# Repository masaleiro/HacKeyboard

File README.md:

# HacKeyboard

Open hardware mechanical keyboard, by Mário Saleiro

HacKeyboard is a mechanical keyboard built from scratch using SMK Alps Mount switches from an old Monterey K108 keyboard and Alps compatible keycaps from an old NGS keyboard.

It has several features that are not usually found in commercial keyboards:
- Internal keylogger;
- Macro recording capabilites;
- Internal USB Hub 2.0;
- Internal (hidden) 8GB flash drive;
- Micro USB Port for connecting peripherals;
- Customizable LED colors;
- Customizable LED effects;

The whole build process is documented and available here: http://www.instructables.com/id/HacKeyboard-a-mechanical-keyboard-built-from-scrat/

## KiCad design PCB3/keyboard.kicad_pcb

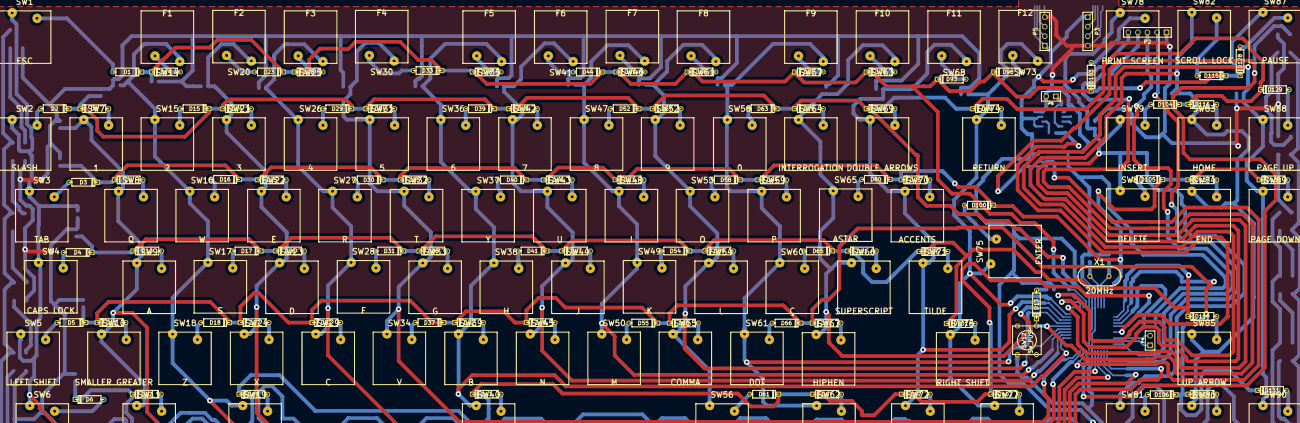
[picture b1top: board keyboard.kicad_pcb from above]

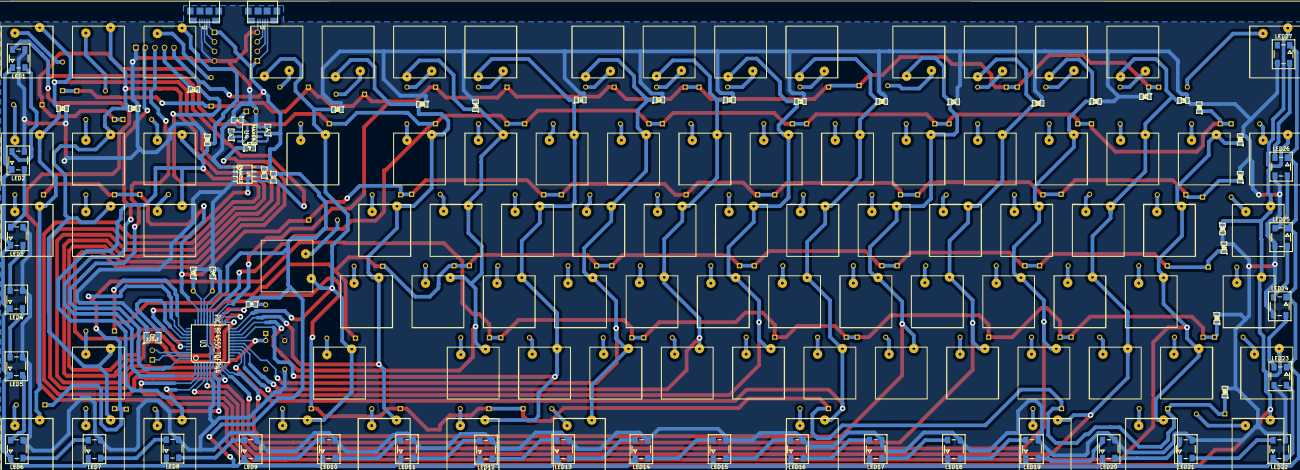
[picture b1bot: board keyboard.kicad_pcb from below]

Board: 2 copper layers, 250 parts (66 on the bottom side), 160 nets.

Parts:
C1: 100nF; SM0805
C2: 220uF; SM1210
C3, C4, C5: C; SM0805
C6, C7: 22pF; SM0805
D1, D2, D3, D4, D5, D6, D8, D9, D10, D11, D12, D14, D15, D16, D17, D18, D19, D23, D24, D25, D26, D27, D28, D29, D30, D31, D32, D33, D34, D35, D36, D37, D38, D39, D40, D41, D42, D43, D44, D45, D46, D47, D48, D51, D52, D53, D54, D55, D56, D57, D58, D59, D60, D61, D62, D63, D64, D65, D66, D67, D78, D79, D80, D81, D82, D93, D94, D95, D96, D97, D98, D99, D100, D101, D102, D103, D104, D105, D106, D115, D116, D117, D118, D119, D128, D129, D130, D131: DIODE; D3
D13: 1N4148; D3
LED1, LED2, LED3, LED4, LED5, LED6, LED7, LED8, LED9, LED10, LED11, LED12, LED13, LED14, LED15, LED16, LED17, LED18, LED19, LED20, LED21, LED22, LED23, LED24, LED25, LED26, LED27: WS2812B; PLCC4-5050
P2: PROG_CONN; PIN_ARRAY_5x1
P3, P5: CONN_4; PIN_ARRAY_4x1
P4, P6: CONN_2; PIN_ARRAY_2X1
R1: R; SM0805
R2, R6, R7: 1K; SM0805
R51, R52, R53, R54, R55, R56, R57, R58, R59, R60, R61, R62, R63, R64, R65, R66, R67, R68, R69, R70, R71, R72, R73: 10K; SM0805
SW1: ESC; ALPS-SWITCH
SW2: SLASH; ALPS-SWITCH
SW3: TAB; ALPS-SWITCH
SW4: CAPS LOCK; ALPS-SWITCH
SW5: LEFT SHIFT; ALPS-SWITCH
SW6: LEFT CONTROL; ALPS-SWITCH
SW7: 1; ALPS-SWITCH
SW8: Q; ALPS-SWITCH
SW9: A; ALPS-SWITCH
SW10: SMALLER GREATER; ALPS-SWITCH
SW11: LEFT SUPER; ALPS-SWITCH
SW12: SW_PUSH; SW_PUSH_SMALL
SW14: F1; ALPS-SWITCH
SW15: 2; ALPS-SWITCH
SW16: W; ALPS-SWITCH
SW17: S; ALPS-SWITCH
SW18: Z; ALPS-SWITCH
SW19: LEFT ALT; ALPS-SWITCH
SW20: F2; ALPS-SWITCH
SW21: 3; ALPS-SWITCH
SW22: E; ALPS-SWITCH
SW23: D; ALPS-SWITCH
SW24: X; ALPS-SWITCH
SW25: F3; ALPS-SWITCH
SW26: 4; ALPS-SWITCH
SW27: R; ALPS-SWITCH
SW28: F; ALPS-SWITCH
SW29: C; ALPS-SWITCH
SW30: F4; ALPS-SWITCH
SW31: 5; ALPS-SWITCH
SW32: T; ALPS-SWITCH
SW33: G; ALPS-SWITCH
SW34: V; ALPS-SWITCH
SW35: F5; ALPS-SWITCH
SW36: 6; ALPS-SWITCH
SW37: Y; ALPS-SWITCH
SW38: H; ALPS-SWITCH
SW39: B; ALPS-SWITCH
SW40: SPACEBAR; ALPS-SWITCH
SW41: F6; ALPS-SWITCH
SW42: 7; ALPS-SWITCH
SW43: U; ALPS-SWITCH
SW44: J; ALPS-SWITCH
SW45: N; ALPS-SWITCH
SW46: F7; ALPS-SWITCH
SW47: 8; ALPS-SWITCH
SW48: I; ALPS-SWITCH
SW49: K; ALPS-SWITCH
SW50: M; ALPS-SWITCH
SW51: F8; ALPS-SWITCH
SW52: 9; ALPS-SWITCH
SW53: O; ALPS-SWITCH
SW54: L; ALPS-SWITCH
SW55: COMMA; ALPS-SWITCH
SW56: RIGHT ALT; ALPS-SWITCH
SW57: F9; ALPS-SWITCH
SW58: 0; ALPS-SWITCH
SW59: P; ALPS-SWITCH
SW60: Ç; ALPS-SWITCH
SW61: DOT; ALPS-SWITCH
SW62: RIGHT SUPER; ALPS-SWITCH
SW63: F10; ALPS-SWITCH
SW64: INTERROGATION; ALPS-SWITCH
SW65: ASTAR; ALPS-SWITCH
SW66: SUPERSCRIPT; ALPS-SWITCH
SW67: HIPHEN; ALPS-SWITCH
SW68: F11; ALPS-SWITCH
SW69: DOUBLE ARROWS; ALPS-SWITCH
SW70: ACCENTS; ALPS-SWITCH
SW71: TILDE; ALPS-SWITCH
SW72: MENU; ALPS-SWITCH
SW73: F12; ALPS-SWITCH
SW74: RETURN; ALPS-SWITCH
SW75: ENTER; ALPS-SWITCH
SW76: RIGHT SHIFT; ALPS-SWITCH
SW77: RIGHT CONTROL; ALPS-SWITCH
SW78: PRINT SCREEN; ALPS-SWITCH
SW79: INSERT; ALPS-SWITCH
SW80: DELETE; ALPS-SWITCH
SW81: LEFT ARROW; ALPS-SWITCH
SW82: SCROLL LOCK; ALPS-SWITCH
SW83: HOME; ALPS-SWITCH
SW84: END; ALPS-SWITCH
SW85: UP ARROW; ALPS-SWITCH
SW86: DOWN ARROW; ALPS-SWITCH
SW87: PAUSE; ALPS-SWITCH
SW88: PAGE UP; ALPS-SWITCH
SW89: PAGE DOWN; ALPS-SWITCH
SW90: RIGHT ARROW; ALPS-SWITCH
U1: MICRO-B_USB_CHG; MICRO-B_USB
U2: MICRO-B_USB_HUB; MICRO-B_USB
U3: PIC18F4550_TQFP44; TQFP44
U4: MAX682; SO8E
U5: 24AA512; so-8
X1: 20MHz; HC-49V

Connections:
/C1: R57.1, SW1.1, SW2.1, SW3.1, SW4.1, SW5.1, SW6.1, U3.2
/C2: R59.1, SW7.1, SW8.1, SW9.1, SW10.1, SW11.1, U3.3
/C3: R61.1, SW14.1, SW15.1, SW16.1, SW17.1, SW18.1, SW19.1, U3.4
/C4: R63.1, SW20.1, SW21.1, SW22.1, SW23.1, SW24.1, U3.5
/C5: R65.1, SW25.1, SW26.1, SW27.1, SW28.1, SW29.1, U3.10
/C6: R67.1, SW30.1, SW31.1, SW32.1, SW33.1, SW34.1, U3.11
/C7: R68.1, SW35.1, SW36.1, SW37.1, SW38.1, SW39.1, SW40.1, U3.14
/C8: R69.1, SW41.1, SW42.1, SW43.1, SW44.1, SW45.1, U3.15
/C9: R70.1, SW46.1, SW47.1, SW48.1, SW49.1, SW50.1, U3.16
/C10: R71.1, SW51.1, SW52.1, SW53.1, SW54.1, SW55.1, SW56.1, U3.17
/C11: R72.1, SW57.1, SW58.1, SW59.1, SW60.1, SW61.1, SW62.1, U3.19
/C12: R73.1, SW63.1, SW64.1, SW65.1, SW66.1, SW67.1, U3.20
/C13: R58.2, SW68.1, SW69.1, SW70.1, SW71.1, SW72.1, U3.21
/C14: R60.2, SW73.1, SW74.1, SW75.1, SW76.1, SW77.1, U3.22
/C15: R62.2, SW78.1, SW79.1, SW80.1, SW81.1, U3.23
/C16: R64.2, SW82.1, SW83.1, SW84.1, SW85.1, SW86.1, U3.24
/C17: R66.2, SW87.1, SW88.1, SW89.1, SW90.1, U3.25
/GND: C2.1, C3.2, C5.2, C6.2, C7.2, LED1.3, LED2.3, LED3.3, LED4.3, LED5.3, LED6.3, LED7.3, LED8.3, LED9.3, LED10.3, LED11.3, LED12.3, LED13.3, LED14.3, LED15.3, LED16.3, LED17.3, LED18.3, LED19.3, LED20.3, LED21.3, LED22.3, LED23.3, LED24.3, LED25.3, LED26.3, LED27.3, P2.1, P3.4, P5.4, P6.2, R51.2, R52.2, R53.2, R54.2, R55.2, R56.2, R57.2, R58.1, R59.2, R60.1, R61.2, R62.1, R63.2, R64.1, R65.2, R66.1, R67.2, R68.2, R69.2, R70.2, R71.2, R72.2, R73.2, SW12.1, U1.5, U2.5, U3.6, U3.29, U4.4, U4.5, U5.1, U5.2, U5.3, U5.4, U5.7
/R1: D1.2, D14.2, D23.2, D28.2, D33.2, D38.2, D44.2, D51.2, D56.2, D62.2, D78.2, D93.2, D98.2, D103.2, D115.2, D128.2, R51.1, U3.26
/R2: D2.2, D8.2, D15.2, D24.2, D29.2, D34.2, D39.2, D45.2, D52.2, D57.2, D63.2, D79.2, D94.2, D99.2, D104.2, D116.2, D129.2, R52.1, U3.27
/R3: D3.2, D9.2, D16.2, D25.2, D30.2, D35.2, D40.2, D46.2, D53.2, D58.2, D64.2, D80.2, D95.2, D100.2, D105.2, D117.2, D130.2, R53.1, U3.32
/R4: D4.2, D10.2, D17.2, D26.2, D31.2, D36.2, D41.2, D47.2, D54.2, D59.2, D65.2, D81.2, D96.2, D101.2, D118.2, R54.1, U3.35
/R5: D5.2, D11.2, D18.2, D27.2, D32.2, D37.2, D42.2, D48.2, D55.2, D60.2, D66.2, D82.2, D106.2, D119.2, D131.2, R55.1, U3.36
/R6: D6.2, D12.2, D19.2, D43.2, D61.2, D67.2, D97.2, D102.2, R56.1, U3.38
/RST: C1.2, D13.2, SW12.2, U3.18
/Rx: P2.2, U3.1
/SCK: R6.1, U3.9, U5.6
/SDA: LED1.4, R7.2, U3.8, U5.5
/SW_PEN: R1.1, U3.40
/Tx: P2.3, U3.44
/VCC: C3.1, LED1.1, LED2.1, LED3.1, LED4.1, LED5.1, LED6.1, LED7.1, LED8.1, LED9.1, LED10.1, LED11.1, LED12.1, LED13.1, LED14.1, LED15.1, LED16.1, LED17.1, LED18.1, LED19.1, LED20.1, LED21.1, LED22.1, LED23.1, LED24.1, LED25.1, LED26.1, LED27.1, P2.5, P3.1, P5.1, R2.2, R6.2, R7.1, U1.1, U2.1, U3.7, U3.28, U4.1, U4.3, U5.8
/VCC2: C5.1, P6.1, U4.8
unnamed: C1.1, P2.4
unnamed: C2.2, U3.37
unnamed: D115.1, SW82.2
unnamed: D130.1, SW89.2
unnamed: D129.1, SW88.2
unnamed: D128.1, SW87.2
unnamed: D131.1, SW90.2
unnamed: D116.1, SW83.2
unnamed: D117.1, SW84.2
unnamed: D118.1, SW85.2
unnamed: D119.1, SW86.2
unnamed: D13.1, R2.1
unnamed: P4.2, U3.42
unnamed: P4.1, U3.43
unnamed: P5.3, U1.3
unnamed: P5.2, U1.2
unnamed: P3.3, U2.3
unnamed: P3.2, U2.2
unnamed: D61.1, SW56.2
unnamed: D60.1, SW55.2
unnamed: D67.1, SW62.2
unnamed: D66.1, SW61.2
unnamed: D65.1, SW60.2
unnamed: D64.1, SW59.2
unnamed: D63.1, SW58.2
unnamed: D62.1, SW57.2
unnamed: D46.1, SW43.2
unnamed: D44.1, SW41.2
unnamed: D45.1, SW42.2
unnamed: D47.1, SW44.2
unnamed: D48.1, SW45.2
unnamed: D53.1, SW48.2
unnamed: D59.1, SW54.2
unnamed: D58.1, SW53.2
unnamed: D57.1, SW52.2
unnamed: D56.1, SW51.2
unnamed: D55.1, SW50.2
unnamed: D54.1, SW49.2
unnamed: D52.1, SW47.2
unnamed: D51.1, SW46.2
unnamed: D102.1, SW77.2
unnamed: D101.1, SW76.2
unnamed: D100.1, SW75.2
unnamed: D99.1, SW74.2
unnamed: D98.1, SW73.2
unnamed: D103.1, SW78.2
unnamed: D106.1, SW81.2
unnamed: D105.1, SW80.2
unnamed: D104.1, SW79.2
unnamed: D82.1, SW67.2
unnamed: D81.1, SW66.2
unnamed: D80.1, SW65.2
unnamed: D79.1, SW64.2
unnamed: D78.1, SW63.2
unnamed: D97.1, SW72.2
unnamed: D93.1, SW68.2
unnamed: D94.1, SW69.2
unnamed: D95.1, SW70.2
unnamed: D96.1, SW71.2
unnamed: LED21.2, LED22.4
unnamed: LED22.2, LED23.4
unnamed: LED16.2, LED17.4
unnamed: LED24.2, LED25.4
unnamed: LED23.2, LED24.4
unnamed: LED20.2, LED21.4
unnamed: LED19.2, LED20.4
unnamed: LED17.2, LED18.4
unnamed: LED18.2, LED19.4
unnamed: C4.1, U4.7
unnamed: C4.2, U4.6
unnamed: R1.2, U4.2
unnamed: LED25.2, LED26.4
unnamed: LED26.2, LED27.4
unnamed: LED4.2, LED5.4
unnamed: LED6.2, LED7.4
unnamed: LED5.2, LED6.4
unnamed: LED7.2, LED8.4
unnamed: LED2.2, LED3.4
unnamed: LED3.2, LED4.4
unnamed: LED1.2, LED2.4
unnamed: LED14.2, LED15.4
unnamed: LED13.2, LED14.4
unnamed: LED8.2, LED9.4
unnamed: LED15.2, LED16.4
unnamed: LED12.2, LED13.4
unnamed: LED11.2, LED12.4
unnamed: LED10.2, LED11.4
unnamed: LED9.2, LED10.4
unnamed: D43.1, SW40.2
unnamed: D42.1, SW39.2
unnamed: D41.1, SW38.2
unnamed: D27.1, SW24.2
unnamed: D26.1, SW23.2
unnamed: D25.1, SW22.2
unnamed: D24.1, SW21.2
unnamed: D23.1, SW20.2
unnamed: D19.1, SW19.2
unnamed: D18.1, SW18.2
unnamed: D17.1, SW17.2
unnamed: D16.1, SW16.2
unnamed: D15.1, SW15.2
unnamed: D39.1, SW36.2
unnamed: D38.1, SW35.2
unnamed: D34.1, SW31.2
unnamed: D32.1, SW29.2
unnamed: D30.1, SW27.2
unnamed: D29.1, SW26.2
unnamed: D28.1, SW25.2
unnamed: C6.1, U3.31, X1.2
unnamed: C7.1, U3.30, X1.1
unnamed: D40.1, SW37.2
unnamed: D37.1, SW34.2
unnamed: D36.1, SW33.2
unnamed: D35.1, SW32.2
unnamed: D31.1, SW28.2
unnamed: D33.1, SW30.2
unnamed: D8.1, SW7.2
unnamed: D14.1, SW14.2
unnamed: D12.1, SW11.2
unnamed: D11.1, SW10.2
unnamed: D10.1, SW9.2
unnamed: D9.1, SW8.2
unnamed: D6.1, SW6.2
unnamed: D1.1, SW1.2
unnamed: D5.1, SW5.2
unnamed: D4.1, SW4.2
unnamed: D3.1, SW3.2
unnamed: D2.1, SW2.2

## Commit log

2015-11-15 Added info to README.md
2015-11-15 Added 3D files, electronics files, source code and precompiled files
